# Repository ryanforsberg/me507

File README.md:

# me507
Cal Poly ME 507 Sumo Bot Project

The latest code is located in /Code/Sumo_RTOS/

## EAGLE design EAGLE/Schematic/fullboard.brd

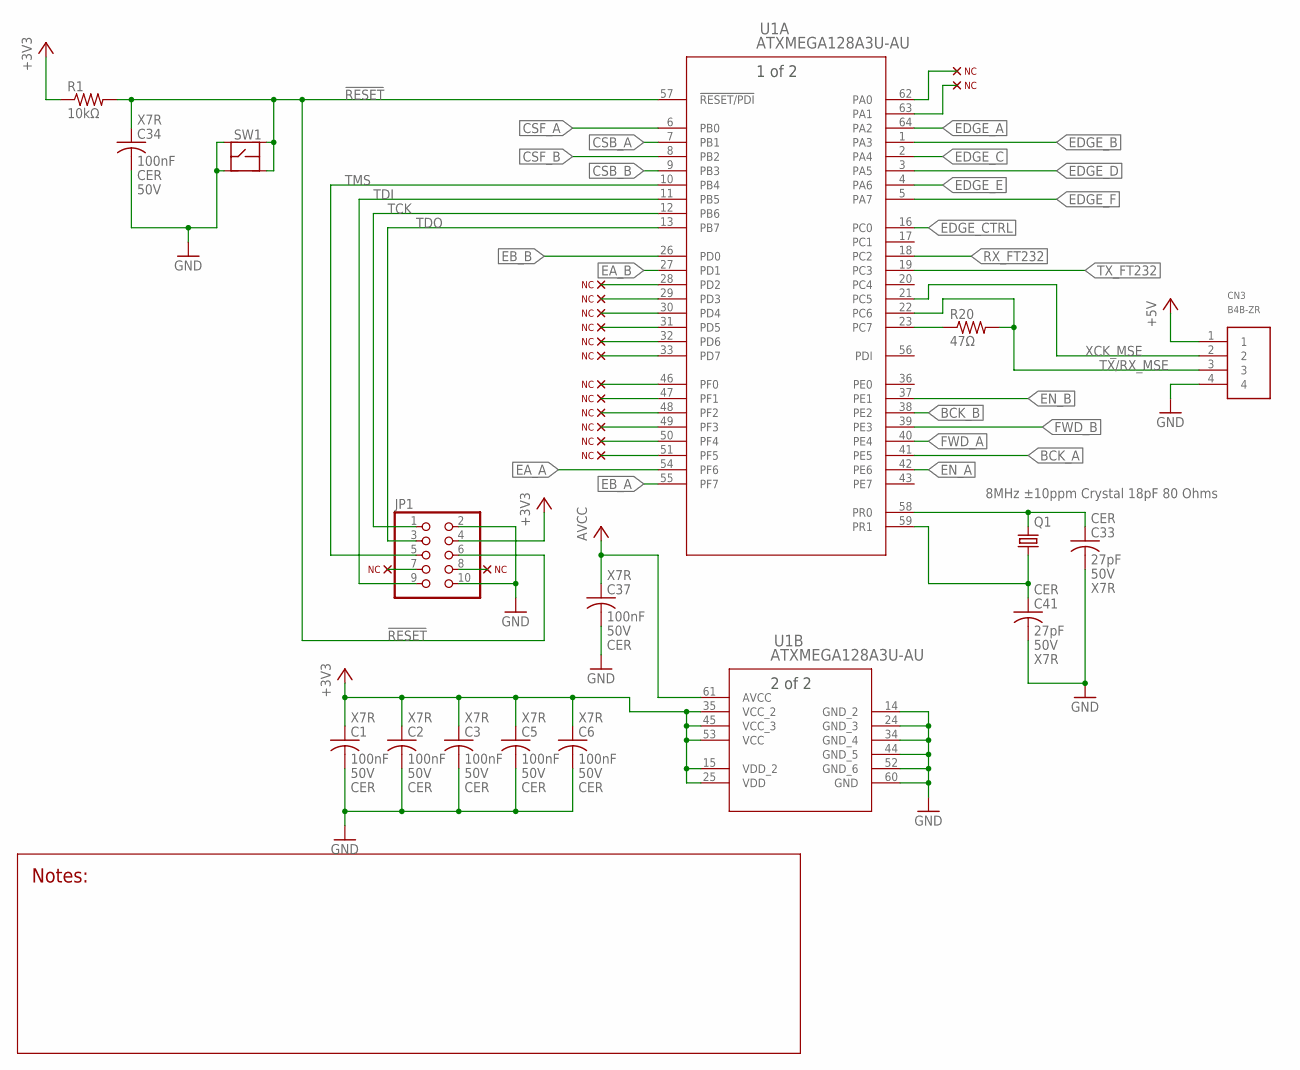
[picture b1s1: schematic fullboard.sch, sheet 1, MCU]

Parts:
C1, C2, C3, C5, C6, C34, C37: 100nF; C0805
C33, C41: 27pF; C0805
CN3: B4B-ZR
JP1: PINHD-2X5; 2X05
Q1: 8MHz ±10ppm Crystal 18pF 80 Ohms; HC49UP
R1: 10kΩ; R0805
R20: 47Ω; R0805
SW1: TR1-SPST; TR1
U1: ATXMEGA128A3U-AU; 64A

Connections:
!RESET: C34.1, JP1.6, R1.2, SW1.3, SW1.4, U1.57 (!RESET/PDI)
+3V3: C1.1, C2.1, C3.1, C5.1, C6.1, JP1.4, R1.1, U1.15 (VDD_2), U1.25 (VDD), U1.35 (VCC_2), U1.45 (VCC_3), U1.53 (VCC); also elsewhere on the board
+5V: CN3.1; also elsewhere on the board
AVCC: C37.1, U1.61 (AVCC); also elsewhere on the board
BCK_A: U1.41 (PE5); also elsewhere on the board
BCK_B: U1.38 (PE2); also elsewhere on the board
CSB_A: U1.7 (PB1); also elsewhere on the board
CSB_B: U1.9 (PB3); also elsewhere on the board
CSF_A: U1.6 (PB0); also elsewhere on the board
CSF_B: U1.8 (PB2); also elsewhere on the board
EA_A: U1.54 (PF6); also elsewhere on the board
EA_B: U1.27 (PD1); also elsewhere on the board
EB_A: U1.55 (PF7); also elsewhere on the board
EB_B: U1.26 (PD0); also elsewhere on the board
EDGE_A: U1.64 (PA2); also elsewhere on the board
EDGE_B: U1.1 (PA3); also elsewhere on the board
EDGE_C: U1.2 (PA4); also elsewhere on the board
EDGE_CTRL: U1.16 (PC0); also elsewhere on the board
EDGE_D: U1.3 (PA5); also elsewhere on the board
EDGE_E: U1.4 (PA6); also elsewhere on the board
EDGE_F: U1.5 (PA7); also elsewhere on the board
EN_A: U1.42 (PE6); also elsewhere on the board
EN_B: U1.37 (PE1); also elsewhere on the board
FWD_A: U1.40 (PE4); also elsewhere on the board
FWD_B: U1.39 (PE3); also elsewhere on the board
GND: C1.2, C2.2, C3.2, C5.2, C6.2, C33.2, C34.2, C37.2, C41.2, CN3.4, JP1.2, JP1.10, SW1.1, SW1.2, U1.14 (GND_2), U1.24 (GND_3), U1.34 (GND_4), U1.44 (GND_5), U1.52 (GND_6), U1.60 (GND); also elsewhere on the board
unnamed: R20.1, U1.23 (PC7)
RX_FT232: U1.18 (PC2); also elsewhere on the board
TCK: JP1.1, U1.12 (PB6)
TDI: JP1.9, U1.11 (PB5)
TDO: JP1.3, U1.13 (PB7)
TMS: JP1.5, U1.10 (PB4)
TX/RX_MSE: CN3.3, R20.2, U1.22 (PC6)
TX_FT232: U1.19 (PC3); also elsewhere on the board
XCK_MSE: CN3.2, U1.21 (PC5)
XTAL1: C41.1, Q1.2, U1.59 (PR1)
XTAL2: C33.1, Q1.1, U1.58 (PR0)

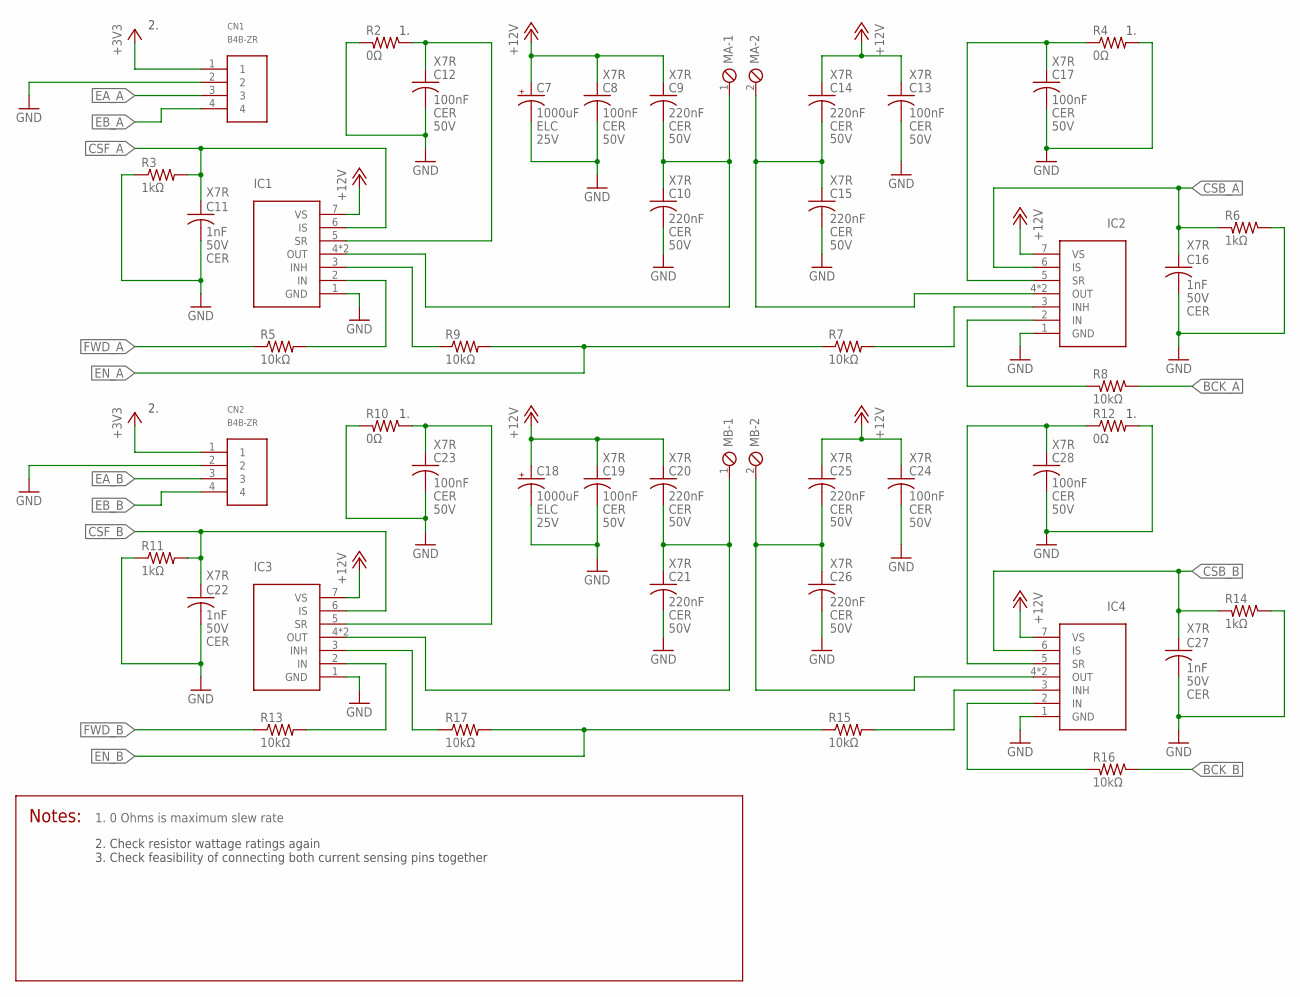
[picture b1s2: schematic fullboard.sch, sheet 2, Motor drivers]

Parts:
C7, C18: 1000uF; E5-10
C8, C12, C13, C17, C19, C23, C24, C28: 100nF; C0805
C9, C10, C14, C15, C20, C21, C25, C26: 220nF; C0805
C11, C16, C22, C27: 1nF; C0805
CN1, CN2: B4B-ZR
IC1, IC2, IC3, IC4: IFX007T; TO127P1500X440-7N
MA: SCREWTERM_2P_508; 2POL508
MB: SCREWTERM_2P_508; 2POL508
R2, R4, R10, R12: 0Ω; R0805
R3, R6, R11, R14: 1kΩ; R0805
R5, R7, R8, R9, R13, R15, R16, R17: 10kΩ; R0805

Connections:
+3V3: CN1.1, CN2.1; also elsewhere on the board
+12V: C7.+, C8.1, C9.1, C13.1, C14.1, C18.+, C19.1, C20.1, C24.1, C25.1, IC1.7 (VS), IC2.7 (VS), IC3.7 (VS), IC4.7 (VS); also elsewhere on the board
BCK_A: R8.1; also elsewhere on the board
BCK_B: R16.1; also elsewhere on the board
CSB_A: C16.1, IC2.6 (IS), R6.2; also elsewhere on the board
CSB_B: C27.1, IC4.6 (IS), R14.2; also elsewhere on the board
CSF_A: C11.1, IC1.6 (IS), R3.2; also elsewhere on the board
CSF_B: C22.1, IC3.6 (IS), R11.2; also elsewhere on the board
EA_A: CN1.3; also elsewhere on the board
EA_B: CN2.3; also elsewhere on the board
EB_A: CN1.4; also elsewhere on the board
EB_B: CN2.4; also elsewhere on the board
EN_A: R7.1, R9.2; also elsewhere on the board
EN_B: R15.1, R17.2; also elsewhere on the board
FWD_A: R5.1; also elsewhere on the board
FWD_B: R13.1; also elsewhere on the board
GND: C7.-, C8.2, C10.2, C11.2, C12.2, C13.2, C15.2, C16.2, C17.2, C18.-, C19.2, C21.2, C22.2, C23.2, C24.2, C26.2, C27.2, C28.2, CN1.2, CN2.2, IC1.1 (GND), IC2.1 (GND), IC3.1 (GND), IC4.1 (GND), R2.2, R3.1, R4.2, R6.1, R10.2, R11.1, R12.2, R14.1; also elsewhere on the board
MA_1: C9.2, C10.1, IC1.4 (OUT), IC1.8 (OUT), MA.1
MA_2: C14.2, C15.1, IC2.4 (OUT), IC2.8 (OUT), MA.2
MB_1: C20.2, C21.1, IC3.4 (OUT), IC3.8 (OUT), MB.1
MB_2: C25.2, C26.1, IC4.4 (OUT), IC4.8 (OUT), MB.2
unnamed: C12.1, IC1.5 (SR), R2.1
unnamed: IC2.3 (INH), R7.2
unnamed: IC2.2 (IN), R8.2
unnamed: C17.1, IC2.5 (SR), R4.1
unnamed: IC1.2 (IN), R5.2
unnamed: C23.1, IC3.5 (SR), R10.1
unnamed: IC4.2 (IN), R16.2
unnamed: IC4.3 (INH), R15.2
unnamed: C28.1, IC4.5 (SR), R12.1
unnamed: IC3.3 (INH), R17.1
unnamed: IC3.2 (IN), R13.2
unnamed: IC1.3 (INH), R9.1

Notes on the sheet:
2. Check resistor wattage ratings again 3. Check feasibility of connecting both current sensing pins together

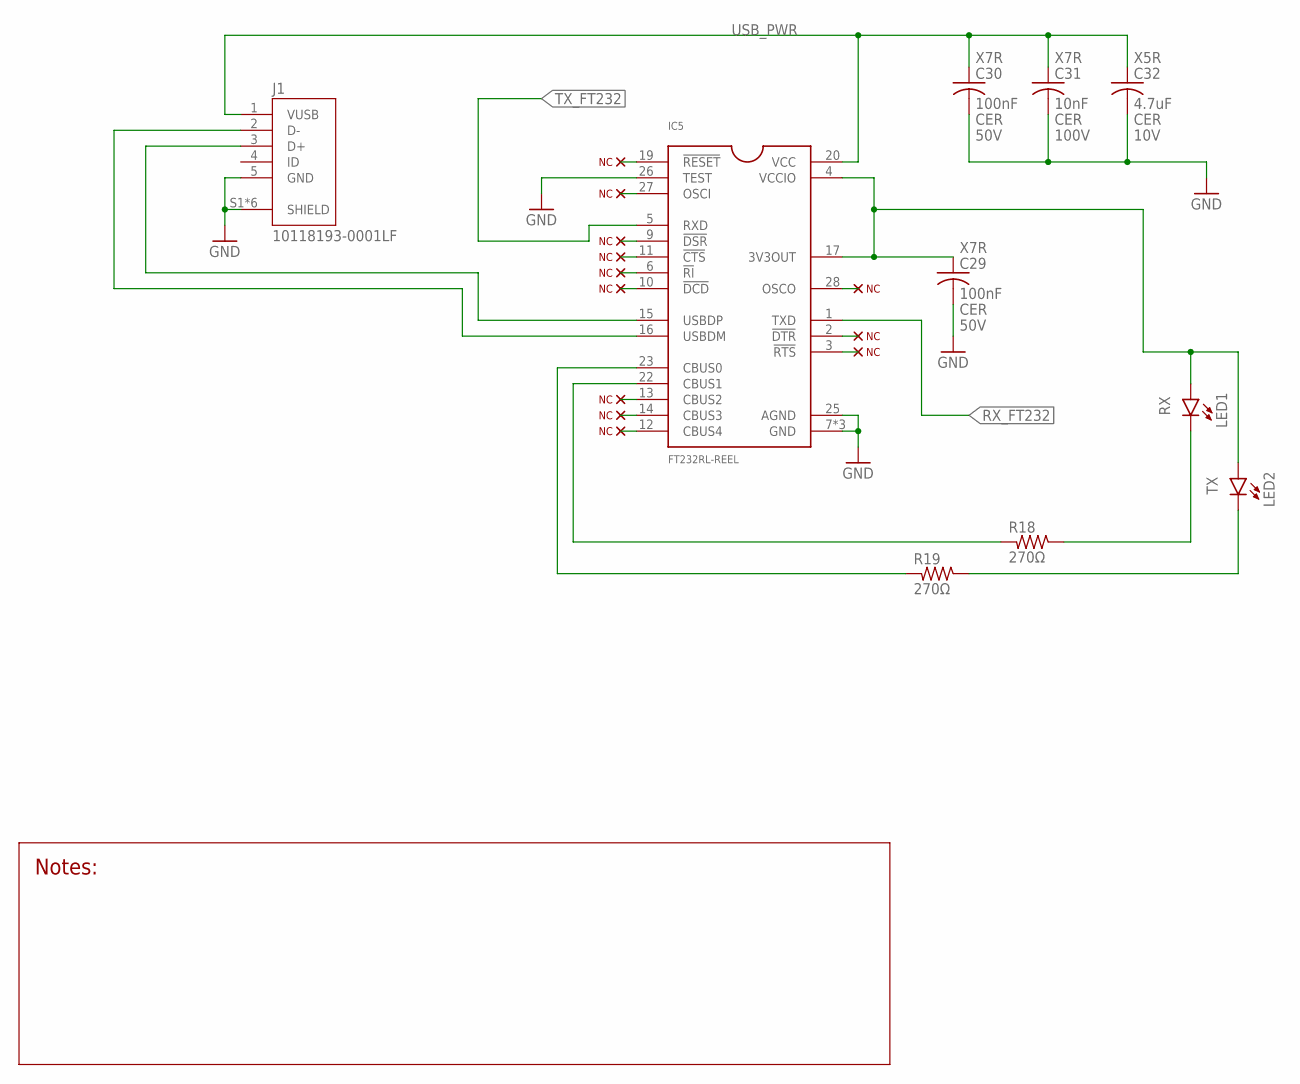
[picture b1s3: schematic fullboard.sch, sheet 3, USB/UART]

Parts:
C29, C30: 100nF; C0805
C31: 10nF; C0805
C32: 4.7uF; C0805
IC5: FT232RL-REEL; SOP65P780X200-28N
J1: 10118193-0001LF; FCI_10118193-0001LF
LED1, LED2: LEDSML0805; SML0805
R18, R19: 270Ω; R0805

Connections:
GND: C29.2, C30.2, C31.2, C32.2, IC5.7 (GND), IC5.18 (GND), IC5.21 (GND), IC5.25 (AGND), IC5.26 (TEST), J1.5 (GND), J1.S1 (SHIELD), J1.S2 (SHIELD), J1.S3 (SHIELD), J1.S4 (SHIELD), J1.S5 (SHIELD), J1.S6 (SHIELD); also elsewhere on the board
unnamed: IC5.16 (USBDM), J1.2 (D-)
unnamed: IC5.15 (USBDP), J1.3 (D+)
unnamed: LED2.C, R19.1
unnamed: IC5.23 (CBUS0), R19.2
unnamed: IC5.22 (CBUS1), R18.2
unnamed: LED1.C, R18.1
RX_FT232: IC5.1 (TXD); also elsewhere on the board
TX_FT232: IC5.5 (RXD); also elsewhere on the board
USB_PWR: C30.1, C31.1, C32.1, IC5.20 (VCC), J1.1 (VUSB)
VCCIO: C29.1, IC5.4 (VCCIO), IC5.17 (3V3OUT), LED1.A, LED2.A

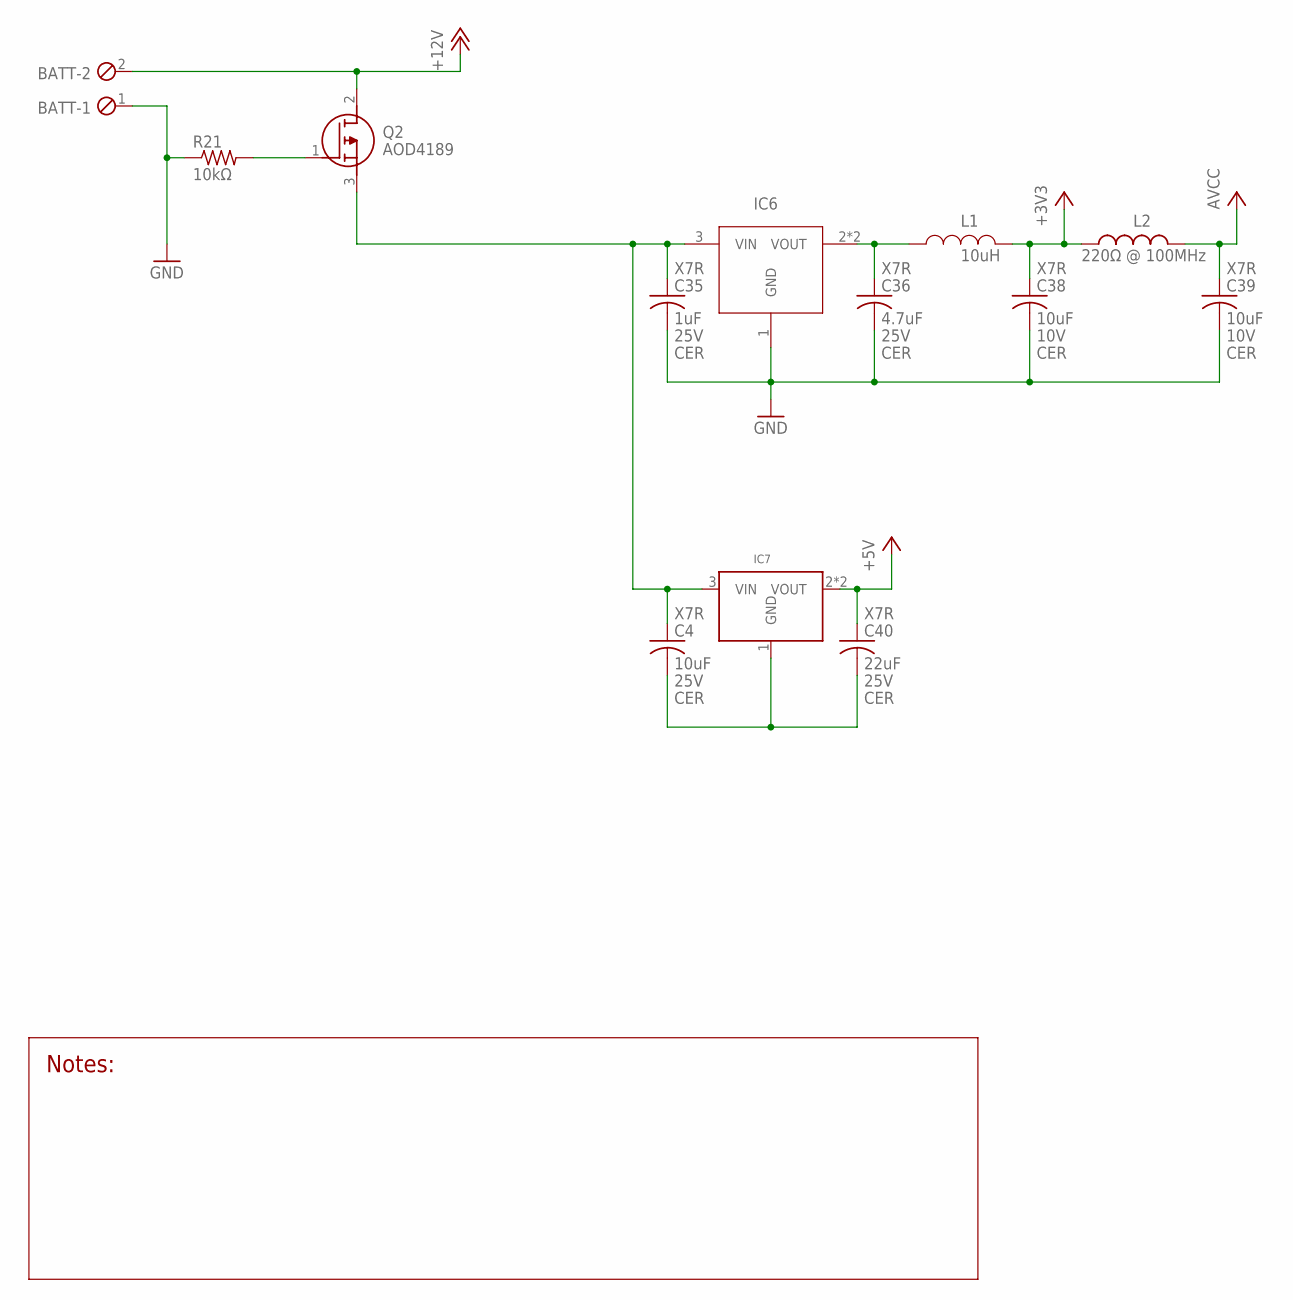
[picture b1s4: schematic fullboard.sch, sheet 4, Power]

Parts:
BATT: SCREWTERM_2P_508; 2POL508
C4, C38, C39: 10uF; C1206
C35: 1uF; C0805
C36: 4.7uF; C1206
C40: 22uF; C1210
IC6: LDL1117S33R; SOT230P700X190-4N
IC7: AZ1117IH; SOT223
L1: RLB0914-100KL; INDRD580W65D870H1300B; RATING 10uH
L2: BLM21PG221SN1D; C0805; RATING 220Ω @ 100MHz
Q2: AOD4189; AOD480
R21: 10kΩ; R0805

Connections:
+3V3: C38.1, L1.1, L2.1; also elsewhere on the board
+5V: C40.1, IC7.2 (VOUT), IC7.4 (VOUT); also elsewhere on the board
+12V: BATT.2, Q2.2 (D); also elsewhere on the board
AVCC: C39.1, L2.2; also elsewhere on the board
GND: BATT.1, C35.2, C36.2, C38.2, C39.2, IC6.1 (GND), R21.1; also elsewhere on the board
unnamed: C4.2, C40.2, IC7.1 (GND)
unnamed: C36.1, IC6.2 (VOUT), IC6.4 (VOUT), L1.2
unnamed: C4.1, C35.1, IC6.3 (VIN), IC7.3 (VIN), Q2.3 (S)
unnamed: Q2.1 (G), R21.2

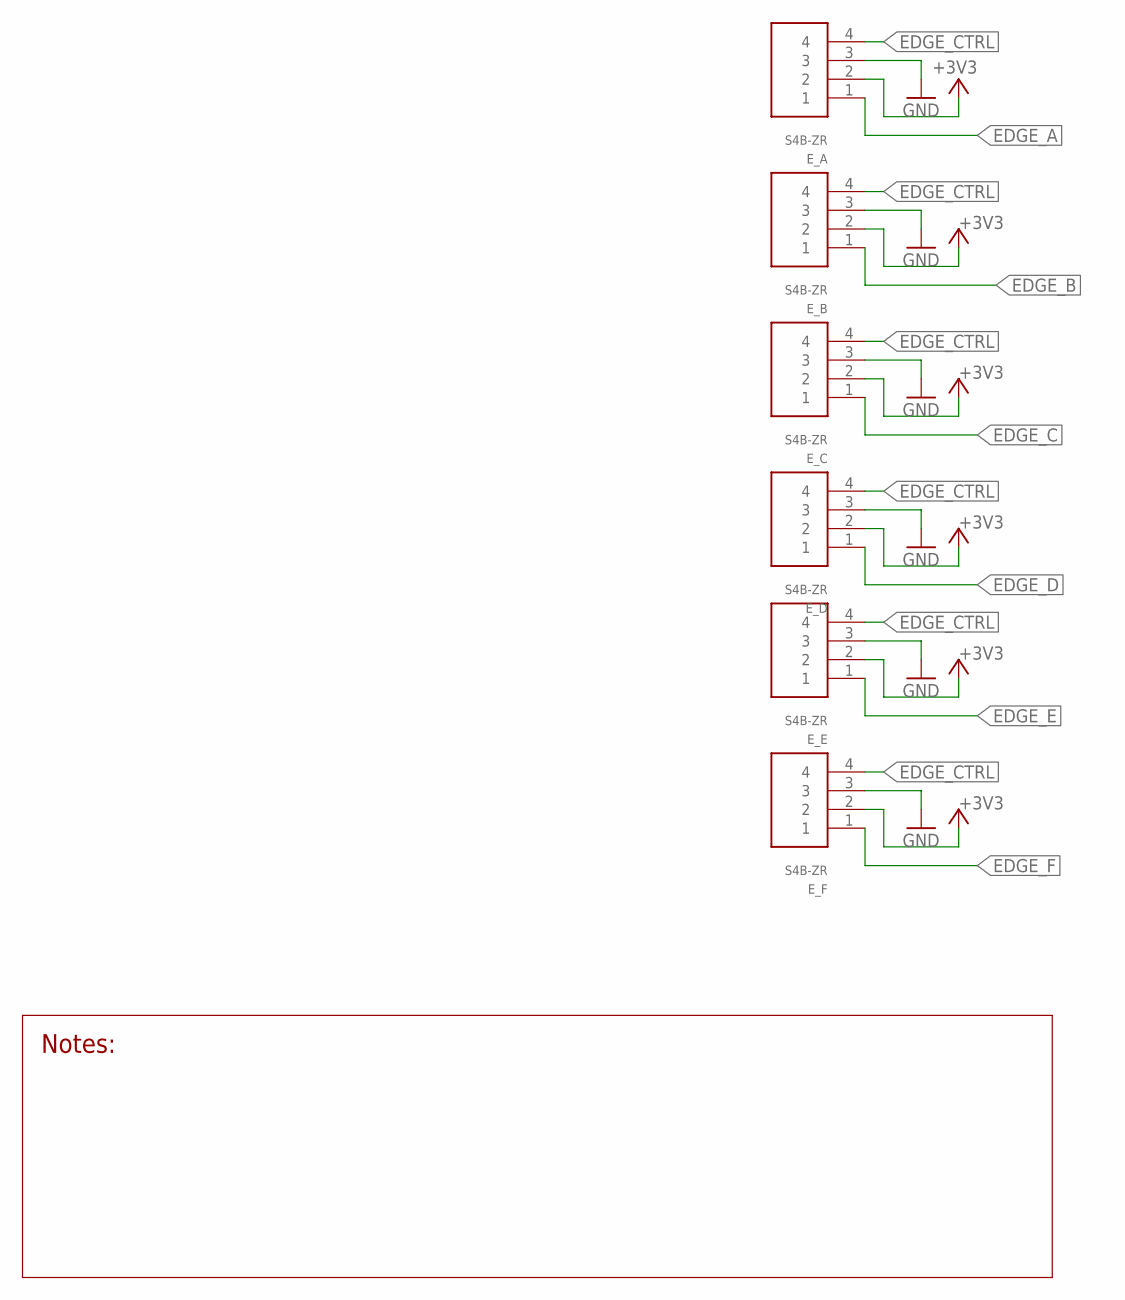
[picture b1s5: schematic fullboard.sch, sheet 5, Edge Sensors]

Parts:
E_A: S4B-ZR
E_B: S4B-ZR
E_C: S4B-ZR
E_D: S4B-ZR
E_E: S4B-ZR
E_F: S4B-ZR

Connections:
+3V3: E_A.2, E_B.2, E_C.2, E_D.2, E_E.2, E_F.2; also elsewhere on the board
EDGE_A: E_A.1; also elsewhere on the board
EDGE_B: E_B.1; also elsewhere on the board
EDGE_C: E_C.1; also elsewhere on the board
EDGE_CTRL: E_A.4, E_B.4, E_C.4, E_D.4, E_E.4, E_F.4; also elsewhere on the board
EDGE_D: E_D.1; also elsewhere on the board
EDGE_E: E_E.1; also elsewhere on the board
EDGE_F: E_F.1; also elsewhere on the board
GND: E_A.3, E_B.3, E_C.3, E_D.3, E_E.3, E_F.3; also elsewhere on the board

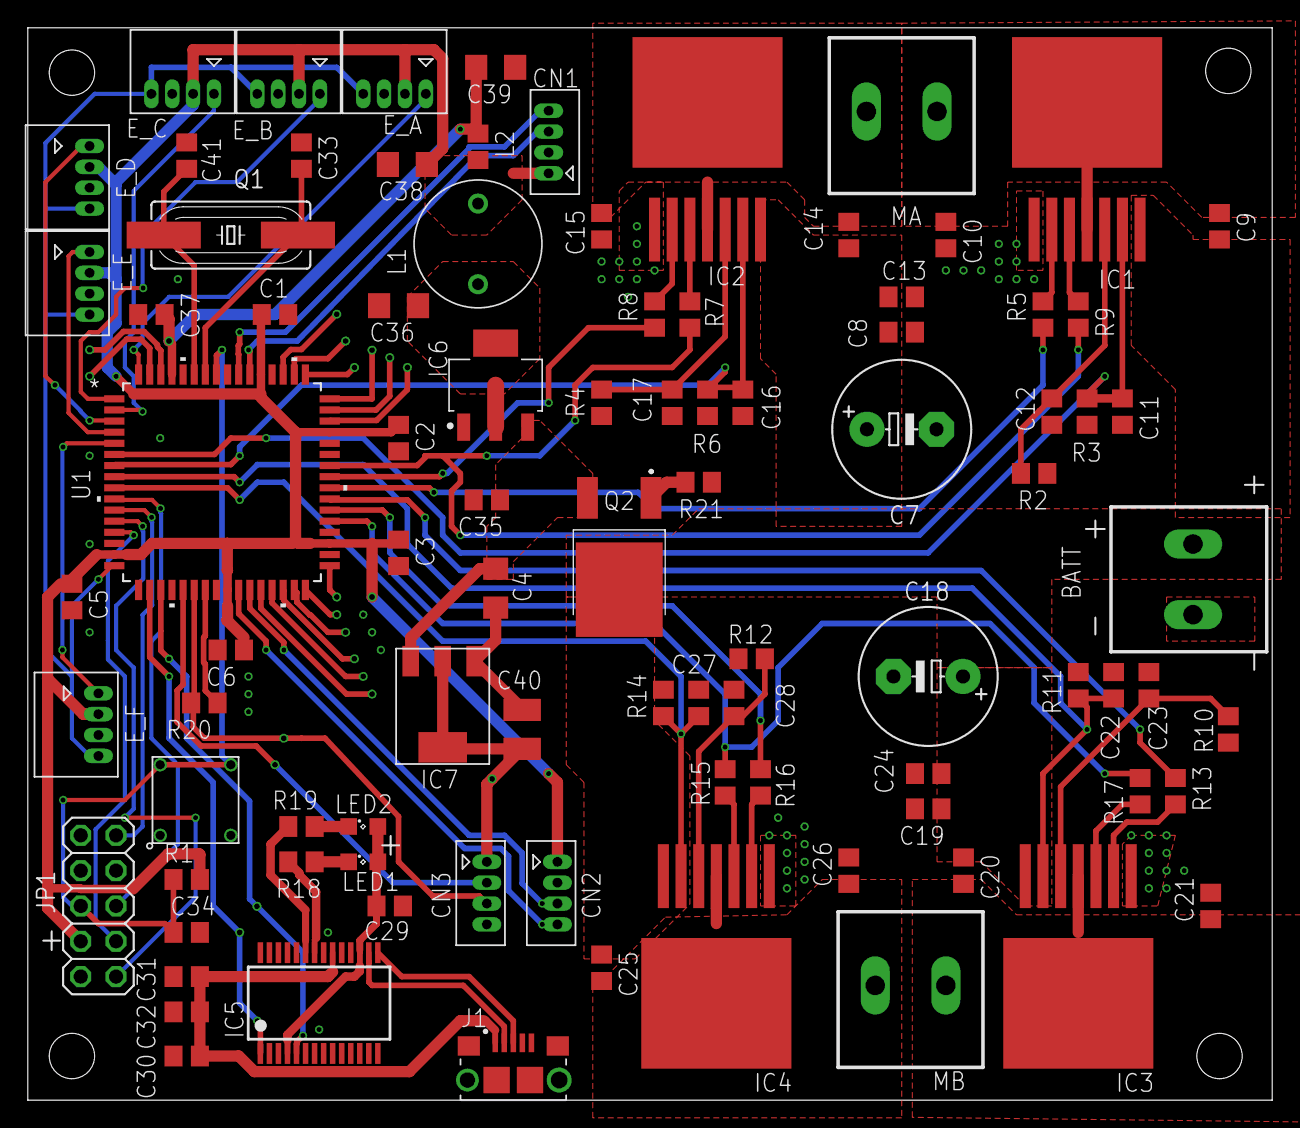
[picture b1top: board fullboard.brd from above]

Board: 2 copper layers, 89.5 x 77.1 mm, 91 parts (0 on the bottom side), 66 nets.

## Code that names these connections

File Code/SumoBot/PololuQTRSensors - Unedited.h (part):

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	// Arduino digital pin 3, sensor 2 is on Arduino digital pin 6,
	// and sensor 3 is on Arduino analog input 1 (digital pin 15).
	// Note that Arduino digital pins 0 - 7 correpsond to port D
	// pins PD0 - PD7, respectively.  Arduino digital pins 8 - 13
	// correspond to port B pins PB0 - PB5.  Arduino analog inputs
	// 0 - 5 are referred to as digital pins 14 - 19 (these are the
	// enumerations you should use for this library) and correspond
	// to port C pins PC0 - PC5.
	
	// 'numSensors' specifies the length of the 'pins' array (i.e. the
	// number of QTR-RC sensors you are using).  numSensors must be 
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	// Arduino analog input 0, sensor 2 is on Arduino analog input 1,
	// and sensor 3 is on Arduino analog input 7.  The ATmega168 has 8
	// total analog input channels (0 - 7) that correspond to port C
	// pins PC0 - PC7.
	
	// 'numSensors' specifies the length of the 'analogPins' array (i.e. the
	// number of QTR-A sensors you are using).  numSensors must be 
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
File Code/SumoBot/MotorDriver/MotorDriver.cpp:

#include MotorDriver.h

/* Motor Driver Task CPP File
* TODO: Verify that compare = 0 is effectively 0% PWM
*		Lol all the testing
*
* DOCUMENTATION:
* Truth Table:
*	Inputs			Direction			Outputs
*	FWD	BCK	LFT	RHT						FWD_A	BCK_A	FWD_B	BCK_B
*	1	0	0	0	Forward				1		0		1		0
*	0	1	0	0	Backward			0		1		0		1
*	0	0	1	0	Pivot Left			0		1		1		0
*	0	0	0	1	Pivot Right			1		0		0		1
*	1	0	1	0	Left Forward Turn	0		0		1		0
*	1	0	0	1	Right Forward Turn	1		0		0		0
*	0	1	1	0	Left Backward Turn	0		0		0		1
*	0	1	0	1	Right Backward Turn	0		1		0		0
*
*/ 
#define period 8000	// used for prescaler and effort calculations

class MotorDriver : public TaskBase
{
protected:
	unit16_t compare = 0;	//start at 0 power
	bool FWD = 0;			//start at 0 movement
	bool BCK = 0;
	bool RHT = 0;
	bool LFT = 0;
	
	// turn pins on/off function
	void set_outputs (bool FWD_A, bool FWD_B, bool BCK_A, bool BCK_B)
	{
		TCE0_CCA = FWD_A*compare; // Hardware pin E4
		TCE0_CCA = BCK_A*compare; // Hardware pin E5
		TCE0_CCC = BCK_B*compare; // Hardware pin E2
		TCE0_CCD = FWD_B*compare; // Hardware pin E3
	}
	
public:
	// constructor
	MotorDriver::MotorDriver (const char* instance_name)
	: TaskBase (instance_name,,)
	//arguments are (in order) - a_name, a_priority, a_stack_size, p_ser_dev)
	{
		
	}
	
	// run function
	void MotorDriver::run (void)
	{
		//!!!---- SETUP ----!!!
		PORTE_DIRSET = 0b01111110;	// config pins 1 through 6 as output
		PORTE_REMAP = 0b00000011;	// remap compare channels A to pin 4.
									// and compare channel B to pin 5.
									// see REMAP (page 151).
		
		TCE0_PER = period;			// set the period to 8000 (see calculation on the project excel sheet)
									// fpwm = fclk/(prescale*(PER+1))
									// aiming for 1 KHz right now (6.6us rise time on half-bridge, recommends at least 10x slower).
		
		// config register B (page 175), single slope PWM, enable compare and capture on channels A, B, C, and D.
		TCE0_CTRLB = TC_WGMODE_SINGLESLOPE_gc | TC0_CCAEN_bm | TC0_CCBEN_bm| TC0_CCCEN_bm| TC0_CCDEN_bm;
		
		set_outputs(0,0,0,0);		// make sure all the directions are off at the start.
		
		TCE0_CTRLA = 0x01;			// turn ON the timer counter - no prescaler
									// see CTRLA (page 175)
									
		PORTE_OUTSET = 6<<0x01 | 1<<0x01; // enable all of the half bridges with pins 1 and 6.
		
		
		//!!!----  RUN  ----!!!
		while(1)
		{
			// pull the new data from the communication variables
			FWD = commForward.get();
			BCK = commBackward.get();
			LFT = commLeft.get();
			RHT = commRight.get();
			
			// convert effort into compare
			compare = effort*period/0xFF;	//convert an 8bit input value to a number between 8000 and 0.
											// compare of 0 is effectively 0% PWM (VERIFY)

			// check for a state change			
			((LFT^RHT)&(!FWD+BCK))?transition_to(3):;   // pivot	(Left XOR Right) AND NOT (Forward OR Back)
			((LFT^RHT)&(FWD^BCK))?transition_to(4):;	// turn		(Left XOR Right) AND (Forward XOR Back)
			((FWD^BCK)&(!(LFT+RHT)))?transition_to(2):;	// straight (Forward XOR Back) AND NOT (Left OR Right)
			(FWD+BCK+LFT+RHT)?transition_to(1):;		// idle
			
			switch (state)
			{
				case (1): //idle state
					set_outputs(0,0,0,0);
					break;
				
				case (2): // forward/back state
					set_outputs(FWD,BCK,BCK,FWD);
					break;
					
				case (3): // pivot state
					set_outputs(RHT,LFT,LFT,RHT);
					break;
				
				case (4): // turn state
					set_outputs(FWD&RHT,FWD&LFT,BCK&RHT,BCK&LFT);
					break;
			};
		}
	}
};

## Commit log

2019-10-25 LED Blink
    Day one of dev board testing with opponent detection
2019-10-25 LED Blink - Frequency change
2019-10-27 Create Fake
2019-10-27 Software Downloads for Driver and Bootloader
2019-10-27 Changes to main.cpp
    First attempt at pulsed PWM of the IR LED - not tested
2019-10-27 Main.cpp
    More complex, but ineffective at this point
2019-10-28 End of day, testing IR Opponent Detection
    Tested continual waveform using Port A5
2019-10-31 Power and Clock schematics
2019-10-31 V0.0 of the board
    Missing:
    * Headers/Connectors for edge sensors
    * Any potential for mouse use (5V regulator system needed)
    * Opponent painting potential
    * Breakout of extra pins
    Other todos:
2019-10-31 Create fsd
2019-10-31 Added libraries
    Added the libraries I've been using - some of the footprints definitely need to be looked at before we order.
2019-10-31 Create asd
2019-10-31 Added datasheets
2019-10-31 V0.1 of the board
    Did some more signal routing, added a connector for the mouse, added a simple 5V regulator circuit
    Still need:
    * Edge sensor connectors
    * Footprint 2x check
    * Probably some other things
2019-10-31 Updated to reflect V0.1 of the board
2019-10-31 All the sheets
2019-10-31 V0.2
    Added Edge Detection and reconfigured other pins
2019-11-01 V0.3
    Don't you dare put a fucking fuse holder on the board.
    Added:
    * Routing all the remaining signals
    * Vias for breakout of leftover pins
    * Now with 200% more suffering
    Still to do:
2019-11-01 V0.4
    Added vias as test points for the two USART channels
2019-11-01 Remove 128A1 datasheet
2019-11-01 Removing more 128a1 datasheets
2019-11-01 We should give our bot whiskers - it's blind AF
2019-11-02 v0.5
    Changes/Status
    * Silkscreen - done, do a final check after walking away for a bit
    * Mounting - #4 screws - moved the ones I could the way I could
    * AREF - should be ok, made vias for use of jumpering if needed.
    Todo:
    * Final check by Charlie
2019-11-05 Create Encoders.txt
    First attempt at encoder setup for Port D, event channel 0, timer channel 0
2019-11-06 v0.6
    Changes
    * Adjusted part locations for increased fastener backup
    * Added text label
2019-11-07 v0.7
    Changes
    * Create solderable vias for +3.3V and +5V
    * Add labels for those vias
2019-11-07 Delete SumoBot.sch
    No longer needed
2019-11-07 v0.8
    Fixed the USB connector footprint
2019-11-08 v0.9
    * Final board used for Fab
2019-11-08 Change to USB conncetor part
    Via and pad fixes
2019-11-08 Creating Gerber folder
2019-11-08 Uploaded gerber files
2019-11-15 Creation of ADC and Edge Sensor Task Project
    Initial ADCA Set Up in progress
2019-11-18 Main Software Folder
    Working on ADC read function
2019-11-19 Continued ADC Reading development
2019-12-03 Create Fucking
2019-12-03 Create Dumb
2019-12-03 Added shares.h, motor driver, and location tasks
2019-12-03 Motor Driver communications truth table - also, deleted fucking.
    * Truth Table:
    * Inputs Direction Outputs
    * FWD BCK LFT RHT FWD_A BCK_A FWD_B BCK_B
    * 1 0 0 0 Forward 1 0 1 0
    * 0 1 0 0 Backward 0 1 0 1
    * 0 0 1 0 Pivot Left 0 1 1 0
2019-12-03 Small changes
    Turn on the enable pins.
2019-12-04 Edge Detection Code
2019-12-05 Edge detecting, Motor driver progressing 5pm
2019-12-05 Fixed major bug w/ Motor Drivers
2019-12-05 Minor testing updates
2019-12-05 Another major bugfix
    I believe the compiler was over-optimizing. It would never enter the test mastermind task.
    Have not tested the latest iteration (waiting on programmer), but previously was able to switch between forward and back via intra-task communication.
2019-12-05 Late night complete
    Edge detection through mastermind to motor drivers active. Still need to test thoroughly
2019-12-05 Late night complete
    edge to mastermind to motor connection
2019-12-08 Doxygen additions
    Added attempts at doxygen documentation for the task_Motor.h/.cpp and shares.h files.
2019-12-08 Creating Doxygen folders
2019-12-08 Adding Doxygen files
    Part 1 of many
2019-12-08 Adding Doxygen Files
    Part 2 of many
2019-12-08 Adding Doxygen files
    Part 3 of many
2019-12-08 Adding Doxygen Files
    Part 4 of 4.
2019-12-08 Additional Doxygen changes
2019-12-09 Doxygen Additions - Ryan
2019-12-10 Doxygen v2.0 - Part 1 of ??
2019-12-10 Doxygen V2.0 - Part 2 of ?
2019-12-10 Doxygen V2.0 - Part 3 of 3
2019-12-10 V1.0
    Final version board design
2019-12-10 Fixing html Begin
2019-12-10 Create PublishingKey

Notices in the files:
Code/SumoBot/PololuQTRSensors - Unedited.h:
Copyright (c) 2008 Pololu Corporation. For more information, see
http://www.pololu.com
notice intact (including the two links above).  Licensed under the
Creative Commons BY-SA 3.0 license:
http://creativecommons.org/licenses/by-sa/3.0
